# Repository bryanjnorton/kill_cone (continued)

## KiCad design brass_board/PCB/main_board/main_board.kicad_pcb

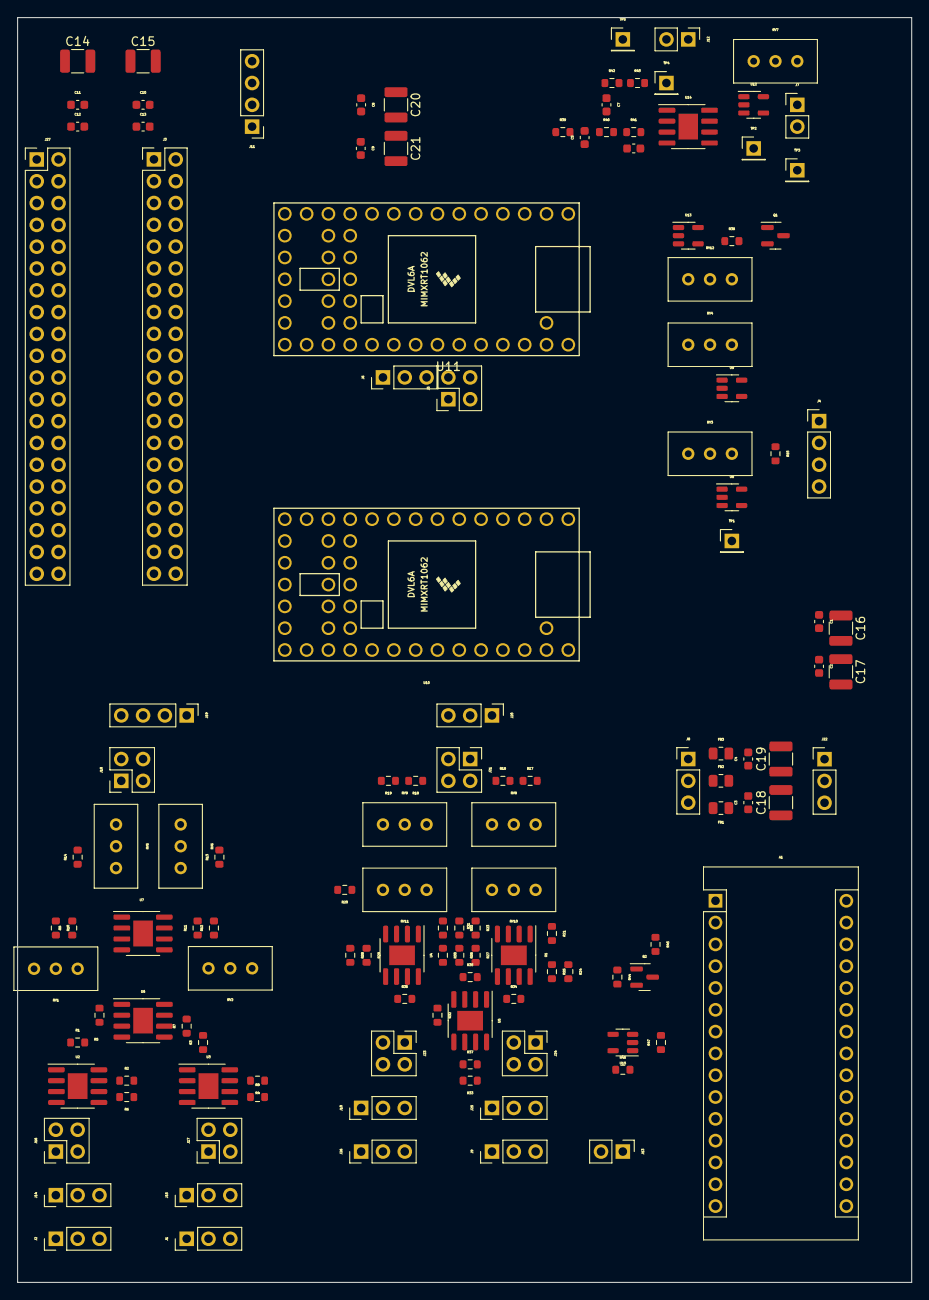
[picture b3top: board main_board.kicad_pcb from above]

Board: 2 copper layers, 104.1 x 147.3 mm, 133 parts (0 on the bottom side), 143 nets, no tracks yet.

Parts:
A1: Arduino_Nano_v3.x; Arduino_Nano
C1, C2, C3, C4, C5, C6, C7, C8, C9, C10, C11, C12, C13: C_Small; C_0603_1608Metric
C14, C15, C16, C17, C18, C19, C20, C21: 100uF; C_1210_3225Metric
FB1, FB2, FB3: FerriteBead_Small; R_0805_2012Metric
J1, J15: Conn_POS_input_B; PinHeader_1x03_P2.54mm_Vertical
J2, J14: Conn_POS_input_A; PinHeader_1x03_P2.54mm_Vertical
J3, J27: Conn_01x40_Male; PinHeader_2x20_P2.54mm_Vertical
J4: Conn_01x04_Male; PinHeader_1x04_P2.54mm_Vertical
J5: Conn_ADC; PinHeader_2x02_P2.54mm_Vertical
J6, J20: Conn_DAC; PinHeader_1x03_P2.54mm_Vertical
J7: Conn_LED_PWM; PinHeader_1x02_P2.54mm_Vertical
J8, J22: Conn_01x03_Male_Power; PinHeader_1x03_P2.54mm_Vertical
J9, J25: Conn_Galvo_A; PinHeader_1x03_P2.54mm_Vertical
J10, J26: Conn_Galvo_B; PinHeader_1x03_P2.54mm_Vertical
J11: Conn_OLED; PinHeader_1x04_P2.54mm_Vertical
J12: Conn_LED_CTL; PinHeader_1x02_P2.54mm_Vertical
J13: Conn_Laser_Trigger; PinHeader_1x02_P2.54mm_Vertical
J16, J17, J18, J21, J23, J24: Conn_02x02_Odd_Even; PinHeader_2x02_P2.54mm_Vertical
J19: Conn_ADC; PinHeader_1x04_P2.54mm_Vertical
Q1, Q2: MMBT3904; SOT-23
R1, R2, R3, R4, R5, R6, R7, R8, R13, R14, R20, R21, R22, R23, R24, R25, R26, R27, R28, R29, R30, R31, R32, R33, R34, R35, R36, R37: 1k; R_0603_1608Metric
R9, R10, R11, R12, R16, R17, R18, R19: 12k; R_0603_1608Metric
R15: 5k; R_0603_1608Metric
R38, R39, R40, R41, R42, R43, R44, R45, R46, R47: R_Small_US; R_0603_1608Metric
RV1, RV2, RV3, RV4, RV5, RV6, RV7, RV8, RV9, RV10, RV11, RV12: 50k; Potentiometer_Bourns_3296W_Vertical
TP1, TP2, TP3, TP4, TP5: TestPoint; PinHeader_1x01_P2.54mm_Vertical
U1, U2, U3, U4, U5, U6, U7, U14: LM393; SOIC-8-1EP_3.9x4.9mm_P1.27mm_EP2.29x3mm
U8, U9, U12, U13, U15: TLV3201; SOT-23-5
U10, U11: Teensy4.0; Teensy40

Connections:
+3V3: C11.1, C12.1, C14.1, J3.1, J3.17, J11.2, J27.1, J27.17, R15.1, RV4.1, U9.5 (V+)
+5V: A1.30 (VIN), C10.1, C13.1, C15.1, J3.2, J3.4, J27.2, J27.4, R45.1, R46.1, RV3.1, RV7.1, RV12.1, U8.5 (V+), U10.33 (VIN), U11.33 (VIN), U12.5 (V+), U13.5 (V+), U15.5 (V+)
+15V: C1.1, C3.1, C8.1, C16.1, C18.1, C20.1, FB1.1, J22.3, RV1.1, RV2.1, RV8.1, RV9.1, U1.8 (V+), U2.8 (V+), U3.8 (V+), U4.8 (V+), U5.8 (V+), U6.8 (V+), U7.8 (V+), U14.8 (V+)
-15V: C2.2, C4.2, C9.2, C17.2, C19.2, C21.2, FB3.1, J22.1, RV1.3, RV2.3, RV8.3, RV9.3, U1.4 (V-), U2.4 (V-), U3.4 (V-), U4.4 (V-), U5.4 (V-), U6.4 (V-), U7.4 (V-), U14.4 (V-)
GND: A1.4 (GND), A1.29 (GND), C1.2, C2.1, C3.2, C4.1, C5.1, C6.2, C8.2, C9.1, C10.2, C11.2, C12.2, C13.2, C14.2, C15.2, C16.2, C17.1, C18.2, C19.1, C20.2, C21.1, FB2.2, J1.2, J2.2, J3.6, J3.9, J3.14, J3.20, J3.25, J3.30, J3.34, J3.39, J4.1, J4.2, J5.1, J5.3, J6.2, J7.1, J9.1, J10.1, J11.1, J12.1, J13.2, J14.2, J15.2, J19.1, J19.3, J20.2, J22.2, J25.1, J26.1, J27.6, J27.9, J27.14, J27.20, J27.25, J27.30, J27.34, J27.39, Q1.1 (E), Q2.1 (E), R5.2, R7.2, R13.2, R14.2, R20.2, R21.2, R22.1, R23.1, R26.1, R27.1, R28.1, R29.1, R32.1, R33.1, R43.2, R47.2, RV3.3, RV4.3, RV7.3, RV12.3, U8.2 (V-), U9.2 (V-), U10.1 (GND), U10.17 (GND), U10.32 (GND), U11.1 (GND), U11.17 (GND), U11.32 (GND), U12.2 (V-), U13.2 (V-), U15.2 (V-)
LED_trigger: J4.3, R15.2, TP2.1, U9.3 (+), U12.3 (+)
unnamed: A1.5 (D2), Q2.3 (C), R45.2
unnamed: A1.7 (D4), U15.3 (+)
unnamed: C5.2, R39.2, R40.1
unnamed: C6.1, R41.2, U14.3 (+)
unnamed: C7.1, R42.1, TP4.1, U14.1, U14.2 (-)
unnamed: C7.2, R40.2, R41.1
unnamed: FB1.2, J8.3
unnamed: FB2.1, J8.2
unnamed: FB3.2, J8.1
unnamed: J1.1, J15.1, J17.1
unnamed: J1.3, J15.3, J17.3
unnamed: J4.4, TP1.1, U8.4
unnamed: J7.2, TP3.1, U12.4
unnamed: J10.2, J23.4, J26.2
unnamed: J10.3, J23.2, J26.3
unnamed: J3.5, J11.3, J27.5
unnamed: J3.3, J11.4, J27.3
unnamed: J12.2, R42.2, R43.1, TP5.1
unnamed: J13.1, U15.4
unnamed: J2.1, J14.1, J16.1
unnamed: J2.3, J14.3, J16.3
unnamed: J16.2, U2.3 (+)
unnamed: J16.4, U2.5 (+)
unnamed: J17.2, U3.3 (+)
unnamed: J17.4, U3.5 (+)
unnamed: J18.1, RV5.2, RV5.3, U7.1
unnamed: J5.4, J18.2, J19.4
unnamed: J18.3, RV6.2, RV6.3, U7.7
unnamed: J5.2, J18.4, J19.2
unnamed: J6.1, J20.1, J21.1
unnamed: J6.3, J20.3, J21.3
unnamed: J21.2, R16.1
unnamed: J21.4, R18.1
unnamed: J23.1, R36.2, U4.7
unnamed: J23.3, R37.2, U5.7
unnamed: J24.1, R34.2, U1.7
unnamed: J9.3, J24.2, J25.3
unnamed: J24.3, R35.2, U5.1
unnamed: J9.2, J24.4, J25.2
unnamed: J3.7, J27.7, U9.4, U10.6 (4_BCLK2), U11.6 (4_BCLK2)
unnamed: J3.8, J27.8
unnamed: J3.10, J27.10
unnamed: J3.11, J27.11
unnamed: J3.12, J27.12
unnamed: J3.13, J27.13
unnamed: J3.15, J27.15, U8.3 (+), U10.5 (3_LRCLK2), U11.5 (3_LRCLK2)
unnamed: J3.16, J27.16
unnamed: J3.18, J27.18
unnamed: J3.19, J27.19, U10.14 (12_MISO_MQSL), U11.14 (12_MISO_MQSL)
unnamed: J3.21, J27.21, U10.13 (11_MOSI_CTX1), U11.13 (11_MOSI_CTX1)
unnamed: J3.22, J27.22
unnamed: J3.23, J27.23, U10.20 (13_SCK_CRX1_LED), U11.20 (13_SCK_CRX1_LED)
unnamed: J3.24, J27.24, U10.12 (10_CS_MQSR), U11.12 (10_CS_MQSR)
unnamed: J3.26, J27.26
unnamed: J3.27, J27.27
unnamed: J3.28, J27.28
unnamed: J3.29, J27.29, U13.3 (+)
unnamed: J3.31, J27.31
unnamed: J3.32, J27.32, U10.7 (5_IN2), U11.7 (5_IN2)
unnamed: J3.33, J27.33, U10.8 (6_OUT1D), U11.8 (6_OUT1D)
unnamed: J3.35, J27.35
unnamed: J3.36, J27.36
unnamed: J3.37, J27.37
unnamed: J3.38, J27.38
unnamed: J3.40, J27.40
unnamed: Q1.2 (B), R38.2
unnamed: Q1.3 (C), U10.18 (PROGRAM), U11.18 (PROGRAM)
unnamed: Q2.2 (B), R44.2
unnamed: R1.1, U2.1, U2.2 (-)
unnamed: R1.2, R5.1, U6.3 (+)
unnamed: R2.1, U2.6 (_), U2.7
unnamed: R2.2, R6.1, U6.2 (-)
unnamed: R3.1, U3.1, U3.2 (-)
unnamed: R3.2, R7.1, U6.5 (+)
unnamed: R4.1, U3.6 (_), U3.7
unnamed: R4.2, R8.1, U6.6 (_)
unnamed: R6.2, R9.1, U6.1
unnamed: R9.2, R10.1, U7.3 (+)
unnamed: R10.2, RV1.2
unnamed: R8.2, R11.1, U6.7
unnamed: R11.2, R12.2, U7.5 (+)
unnamed: R12.1, RV2.2
unnamed: R13.1, RV6.1, U7.6 (_)
unnamed: R14.1, RV5.1, U7.2 (-)
unnamed: R16.2, R17.1, U1.3 (+)
unnamed: R17.2, RV8.2
unnamed: R18.2, R19.2, U4.3 (+)
unnamed: R19.1, RV9.2
unnamed: R20.1, RV11.1, U4.2 (-)
unnamed: R21.1, RV10.1, U1.2 (-)
unnamed: R22.2, R23.2, U1.5 (+)
unnamed: R24.1, R25.1, RV10.2, RV10.3, U1.1
unnamed: R24.2, R34.1, U1.6 (_)
unnamed: R25.2, R26.2, U5.3 (+)
unnamed: R27.2, R35.1, U5.2 (-)
unnamed: R28.2, R29.2, U4.5 (+)
unnamed: R30.1, R31.1, RV11.2, RV11.3, U4.1
unnamed: R30.2, R36.1, U4.6 (_)
unnamed: R31.2, R32.2, U5.5 (+)
unnamed: R33.2, R37.1, U5.6 (_)
unnamed: R38.1, U13.4
unnamed: R44.1, U10.22 (15_A1_RX3_SPDIF_IN), U11.22 (15_A1_RX3_SPDIF_IN)
unnamed: R46.2, R47.1, U15.1 (-)
unnamed: RV3.2, U8.1 (-)
unnamed: RV4.2, U9.1 (-)
unnamed: RV7.2, U12.1 (-)
unnamed: RV12.2, U13.1 (-)
unnamed: U10.2 (0_RX1_CRX2_CS1), U11.2 (0_RX1_CRX2_CS1)
unnamed: U10.3 (1_TX1_CTX2_MISO1), U11.3 (1_TX1_CTX2_MISO1)
unnamed: U10.9 (7_RX2_OUT1A), U11.9 (7_RX2_OUT1A)
unnamed: U10.10 (8_TX2_IN1), U11.10 (8_TX2_IN1)
unnamed: U10.11 (9_OUT1C), U11.11 (9_OUT1C)
unnamed: U10.15 (VBAT), U11.15 (VBAT)
unnamed: U10.16 (3V3), U11.16 (3V3)
unnamed: U10.19 (ON_OFF), U11.19 (ON_OFF)
unnamed: U10.21 (14_A0_TX3_SPDIF_OUT), U11.21 (14_A0_TX3_SPDIF_OUT)
unnamed: U10.23 (16_A2_RX4_SCL1), U11.23 (16_A2_RX4_SCL1)
unnamed: U10.24 (17_A3_TX4_SDA1), U11.24 (17_A3_TX4_SDA1)
unnamed: U10.25 (18_A4_SDA0), U11.25 (18_A4_SDA0)
unnamed: U10.26 (19_A5_SCL0), U11.26 (19_A5_SCL0)
unnamed: U10.27 (20_A6_TX5_LRCLK1), U11.27 (20_A6_TX5_LRCLK1)
unnamed: U10.28 (21_A7_RX5_BCLK1), U11.28 (21_A7_RX5_BCLK1)
unnamed: U10.29 (22_A8_CTX1), U11.29 (22_A8_CTX1)
unnamed: U10.30 (23_A9_CRX1_MCLK1), U11.30 (23_A9_CRX1_MCLK1)
unnamed: U10.31 (3V3), U11.31 (3V3)
unnamed: U10.34 (VUSB), U11.34 (VUSB)
unnamed: U10.35 (24_A10_TX6_SCL2), U11.35 (24_A10_TX6_SCL2)
unnamed: U10.36 (25_A11_RX6_SDA2), U11.36 (25_A11_RX6_SDA2)
unnamed: U10.37 (26_A12_MOSI1), U11.37 (26_A12_MOSI1)
unnamed: U10.38 (27_A13_SCK1), U11.38 (27_A13_SCK1)
unnamed: U10.39 (28_RX7), U11.39 (28_RX7)
unnamed: U10.40 (29_TX7), U11.40 (29_TX7)
unnamed: U10.41 (30_CRX3), U11.41 (30_CRX3)
unnamed: U10.42 (31_CTX3), U11.42 (31_CTX3)
unnamed: U10.43 (32_OUT1B), U11.43 (32_OUT1B)
unnamed: U10.44 (33_MCLK2), U11.44 (33_MCLK2)
PWM_DAC: R39.1, U10.4 (2_OUT2), U11.4 (2_OUT2)

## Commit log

2022-03-30 init
2022-03-30 added pics of prototype
2022-04-10 REfactor
2022-04-10 Clean up pictures
2022-04-12 updated per Phil's changes
    added pwm filter, fixed some footprints
2022-04-12 Added Arduino
2022-04-12 Added test points and line driver for laser trigger
2022-04-12 First PCB placement
2022-04-13 Placement done
2022-04-13 Added LTspice tests and fixed error on opamp. ready for routing
2022-04-15 Fixed Ferrite Bead
2022-04-15 Sent to Fab
2022-04-15 Added legacy galvo amp
2022-04-15 Added data sheets
2022-04-18 Fixed driver footprint and parts errors: now at Rev1
2022-04-18 More saved to Rev1
2022-04-19 Added optical files
2022-04-19 Fixed windows picture problem
2022-04-20 Added filter order information.
2022-04-28 Fix pin mis-route. Refactor schematic.
    Teensy was connected to wrong audio board pins for I2S TX and RX. Fixed.
    Refactored schematic using busses.
    Added logical schematic symbol for Jetson header.
2022-04-28 Saved by TiddlyWiki
2022-05-02 cad update
2022-05-20 proto parts
2022-05-20 CAD bits update
2022-05-20 Added some pinout images
2022-05-20 Big PCB update: Added LED driver, Added laser interface, Fixed errors from RC1
2022-06-05 LED driver board
2022-06-05 main board updates
2022-06-05 test eq
2022-06-05 clipping check
2022-06-05 3D print parts
2022-06-05 Refactor CAD folder
2022-06-05 Added CAD REV2
2022-06-18 Updates to main board
2022-06-18 LED driver update
2022-06-18 LED board init
2022-06-18 main board update
2022-06-19 Check in for Phil
2022-06-24 More changes, added boot jumper
2022-07-11 main board R2 backup
2022-07-11 LED driver R1 backup
2022-07-11 LED pcb backup
2022-07-11 LED driver old backups
2022-07-11 main board old backups half
2022-07-11 main board old backups other half
2022-11-06 last update
